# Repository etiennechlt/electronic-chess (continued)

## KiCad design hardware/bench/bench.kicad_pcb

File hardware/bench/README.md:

# Banc Nucleo : shield d'alimentation et de liaison du quadrant 2 x 2

Les deux faces tracées par KiCad, pours remplis (`tools/plot.py`) :
la face composants avec sa sérigraphie, puis la face masse vue
retournée, comme on regarde la carte réelle.

Carte générée par `tools/boardgen` (module `bench`) depuis la section
`bench` de `config/board.yaml`, pour le banc de la
[note 19](../../docs/notes/19-cerveau-et-banc-nucleo.md) : une
Nucleo-G474RE (le MCU du cerveau, sa sonde et son port série) qui
mesure le quadrant réduit 2 x 2 (`hardware/quadrant-2x2/`) avec le
firmware du cerveau compilé en `make NUCLEO=1`. Le shield apporte au
quadrant ce que le cerveau lui aurait donné, et rien d'autre.
80 x 56 mm, 2 couches : composants et signaux sur F.Cu, plan de masse
sur B.Cu. Elle s'emboîte sur les quatre embases Arduino de la Nucleo
par des barrettes mâles montées côté cuivre, corps sous la carte.

## Blocs

- **Embases Arduino** (J3 alimentation, J4 analogique, J5 numérique 0 à
  7, J6 numérique 8 à 15) : positions prises sur l'empreinte officielle
  `Arduino_UNO_R3`, contour Uno affleurant au bord ouest, bande de
  11,4 mm à l'est pour le jack et la nappe. Le bus du quadrant est sur
  les broches de `bench.signals` : AMP_OUT (après RC) sur A0, PULSE_EN
  sur A2, MUX_A0 à A2 sur D3, D4, D5, MUX_EN_L sur A5, MUX_EN_H sur A4,
  DAMP_EN_N sur D6, LED_DIN sur D13. Le shield prend le 3,3 V et la
  masse de la Nucleo ; son 5 V ne remonte jamais vers elle (la Nucleo
  reste sur l'USB de sa sonde), VIN, 5V, IOREF, NRST et AREF restent
  ouverts.
- **Entrée 12 V** (J1 jack 5,5 x 2,1 mm, prise vers l'est) : SS34 en
  série contre l'inversion, SMBJ15A vers la masse, fusible 1 A, puis
  100 µF, 10 µF et 100 nF : la réserve du rail d'impulsion, comme sur
  le cerveau, dans la colonne centrale entre le jack et le buck.
- **Buck 5 V** (TPS62130, 2,2 µH, DEF haut : PWM forcé) : le rail des
  LED à travers un second fusible 2 A et 100 µF, et l'alimentation du
  tampon LED. Colonne ouest, là où le motif Uno laisse le shield vide.
- **Îlot analogique 5VA** : LP2985-5.0 depuis le 12 V, perle de
  ferrite BLM21PG221, 10 µF et 100 nF, comme sur le cerveau. Le
  cavalier JP1 choisit la source de 5VA_RAW : broches 1 et 2, le LDO
  (défaut) ; 2 et 3, le buck. C'est la comparaison LDO contre buck de la
  mesure M8.
- **Liaison quadrant** : J2, FPC 16 broches Hirose FH12 au brochage du
  quadrant (`plateau.quadrant.link.pinout`), au coin sud-est, nappe
  vers le sud, pastilles vers le nord ; tampon 74AHCT1G125 (3,3 V vers
  5 V) et 470 ohms devant LED_DIN, LED_DOUT sur un point de test ;
  49,9 ohms et 1 nF devant A0, le filtre du cerveau.
- **Points de test** : TP1 LED_END (au coin sud-est, contre le
  connecteur FPC), TP2 5VA, TP3 5V, TP4 3V3, TP5 GND, TP6 VIN, TP7 ADC1
  (AMP_OUT filtré). Le bus de commande (PULSE_EN, DAMP_EN_N, adresses
  du mux) se sonde sur les broches Morpho de la Nucleo, qui doublent
  chaque broche Arduino.

## Ce qui se soude à la main

Le tampon LED, le buck, l'inductance, le LDO, la perle, les diodes,
le jack et le connecteur FPC reprennent les références du cerveau,
code LCSC compris. Les passifs, les quatre barrettes Arduino (côté
cuivre), JP1 et les points de test n'ont pas de code : `jlc-bom.csv`
ne liste que les lignes qui en ont un, le reste se soude à la main ou
attend la passe de sourcing des autres cartes.

## Régénérer

```bash
PYTHONPATH=tools .venv/bin/python -m boardgen build bench --render docs/images/bench.png
/usr/bin/python3 tools/plot.py hardware/bench/bench.kicad_pcb --out docs/images
```

La seconde commande, avec le Python de KiCad, remplit les pours et
trace les deux faces en SVG (`bench-top.svg`, `bench-bottom.svg`).

`tests/test_bench.py` vérifie que chaque signal du bus est sur la
broche du cerveau (sauf DAMP_EN_N, déplacé de PC2 à D6 parce que PC2
n'atteint qu'un connecteur Morpho), que chaque broche d'embase porte
le net que dit le yaml, que la nappe reprend le brochage du quadrant,
et que chaque broche de barrette tombe sur la pastille de l'empreinte
Uno qu'elle représente.

## Routes manuelles

Le routeur seul laissait six nets ouverts et, au DRC de KiCad, une
trentaine de connexions manquantes que son propre bilan ne voyait pas
(couloirs de sortie des vias d'éventail sans cuivre, pistes finissant
sur le coin arrondi d'une pastille, voir la
[note 04](../../docs/notes/04-routeur-et-garanties.md)). La carte se
finit donc comme dans pcbnew, mais dans le générateur, par des routes
manuelles (`hand_routes` de `tools/boardgen/bench.py`) que chaque
build redessine et vérifie :

- **Éventail du FPC** (J2, seize pastilles au pas de 0,5 mm) : pas de
  via d'éventail dans le plan de masse ; chaque broche quitte son
  moignon sur une colonne de 0,2 mm et tourne à sa hauteur dans une
  voie de 0,3 mm, vers l'ouest pour 5VA, AMP_OUT1, 3V3 et 5V_LED, vers
  l'est pour MUX_EN_L, MUX_EN_H, LED_END et PULSE_EN, la broche la
  plus extérieure d'abord, la suivante une voie plus haut, si bien
  qu'aucune voie ne croise une colonne ; les fins de voies sont
  décalées pour laisser un via au bout de chacune. MUX_A0, MUX_A1,
  MUX_A2 et DAMP_EN_N prennent un petit via aux rangées d'éventail et
  passent en face arrière sous le connecteur, puis sous l'embase J5
  jusqu'à leurs broches ; VIN et LED_DIN1 de même vers le nord. Les
  deux broches de masse tombent au plan par un via au bout de leur
  piste d'envol.
- **Bande est** : MUX_EN_L monte en face avant jusqu'à la rangée de J4
  et entre dans la dernière broche par le bout de la rangée, MUX_EN_H
  passe au-dessus de la rangée, PULSE_EN monte en face arrière le long
  du bord (les deux se croiseraient sinon), LED_END rejoint TP1.
- **Face nord** : 3V3 monte à l'ouest de C9, passe sous les embases
  jusqu'à J3, continue vers l'ouest et redescend entre C6 et R3 vers
  TP4 et C14 ; 5V_LED et AMP_OUT1 suivent, une voie plus bas chacune,
  jusqu'au fusible des LED et au filtre de l'ADC, 5V_LED sautant en
  face arrière sur deux millimètres pour franchir la montée de 3V3 ;
  VIN traverse la carte en face arrière à mi-hauteur jusqu'à TP6.
- **Buck** : une barrette de 0,2 mm sur les bouts de moignons relie
  les trois pastilles SW, une autre les trois VIN (le routeur posait
  une piste de puissance le long d'une piste d'envol, à 0,10 mm du
  moignon voisin) ; SW part en face arrière vers l'inductance, VIN vers
  un via à l'est de C4 puis le condensateur d'entrée, la pastille 5 V
  du côté nord suit son couloir de sortie ; les quatre pastilles de
  masse du QFN sont pontées à son pad thermique.
- **Masses murées** : la pastille de masse du LDO (entre ses deux
  VIN) et celle de R4 ont un moignon et un petit via vers le plan.

Chaque route manuelle est vérifiée au build par le contrôle
d'isolement exact contre le cuivre déjà posé ; le routeur part de ces
routes et termine chaque net. Un déplacement de composant qui les
rendrait fausses fait échouer le build.

## Résultat du build

Généré par `python -m boardgen build bench` :

| Composants | Segments | Vias | Nets fermés | Nets ouverts | Défauts d'isolement |
|---|---|---|---|---|---|
| 43 | 263 | 72 | 29 | 0 | 0 |

Tous les nets sont fermés : le contrôle de connexité partagé des
générateurs (`tools/quadgen/connect.py`, chaque net une seule pièce de
cuivre, plan de masse compris, [note 04](../../docs/notes/04-routeur-et-garanties.md))
ne signale rien, `tests/test_bench.py` le vérifie à chaque exécution.

DRC KiCad 7.0.11 (`/usr/bin/python3 tools/drc.py
hardware/bench/bench.kicad_pcb`, zones remplies) : zéro erreur, zéro
élément non connecté ; 83 avertissements, tous ignorables : 43
chemins de bibliothèque des empreintes (la configuration de KiCad ne
connaît pas les bibliothèques par leur nom), 35 de sérigraphie
(références sur une ligne ou une pastille), 5 vias d'éventail du QFN
raccordés d'un seul côté (la route est partie en face avant).

## Gerbers de fabrication

`bench-gerbers.zip` se dépose tel quel chez le fabricant : 2 couches
(F.Cu, B.Cu), la pâte de la face composants, les deux sérigraphies,
les deux masques, le contour et les perçages Excellon séparés (PTH et
NPTH), plus le fichier de tâche `.gbrjob`. 1,6 mm, finition HASL sans
plomb ou ENIG ; les options de commande et la nomenclature sont dans
la [note 20](../../docs/notes/20-tuto-banc.md), section 3.

À côté de l'archive, `<carte>-gerbers.sha256` porte l'empreinte de la
carte tracée et celle de l'archive. À vérifier avant toute commande :

```bash
cd hardware/bench && sha256sum -c bench-gerbers.sha256
```

Options écran par écran, quantités et décisions à trancher : la
[note 23](../../docs/notes/23-commande-jlcpcb.md).

```bash
/usr/bin/python3 tools/gerbers.py hardware/bench/bench.kicad_pcb
```

Avec le Python de KiCad : l'outil remplit les pours d'une copie de la
carte avant de tracer (sans ce remplissage le plan de masse de B.Cu
sort vide), lit le jeu de couches sur la carte, et refuse d'exporter
tant qu'une pastille reste non connectée. Le dossier `gerbers/` qu'il
écrit n'est pas versionné ; l'archive l'est.

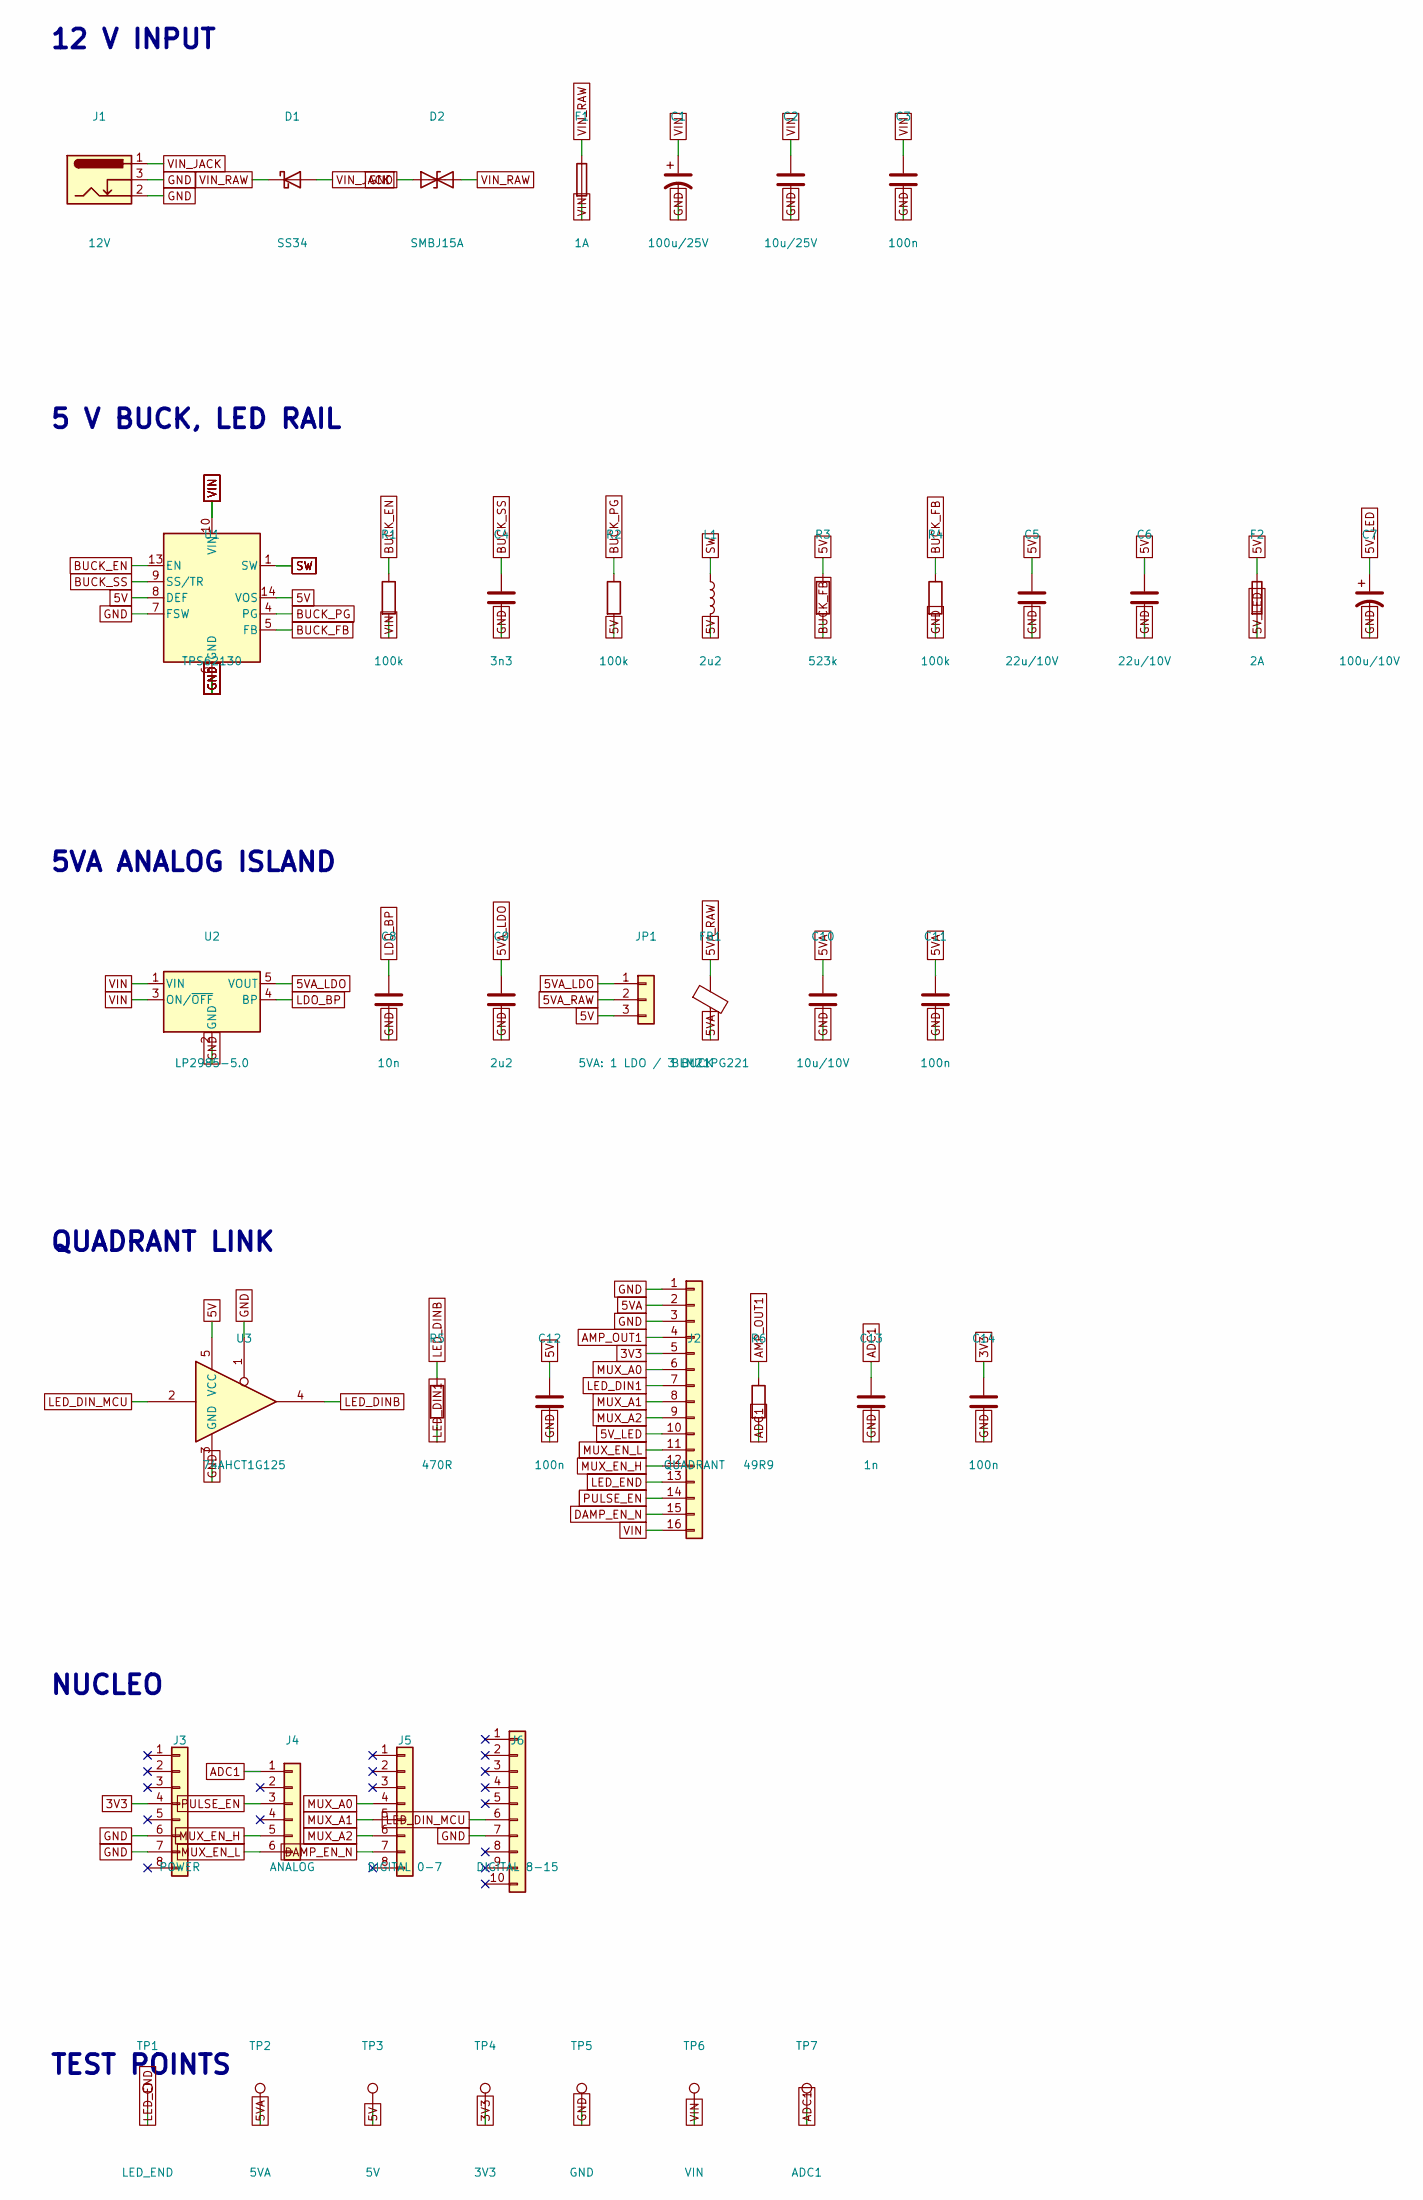
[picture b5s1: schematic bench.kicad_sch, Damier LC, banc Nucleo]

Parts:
C1: 100u/25V; CP_Elec_6.3x7.7
C2: 10u/25V; C_1206_3216Metric
C3, C11, C12, C14: 100n; C_0603_1608Metric
C4: 3n3; C_0603_1608Metric
C5, C6: 22u/10V; C_1206_3216Metric
C7: 100u/10V; CP_Elec_6.3x7.7
C8: 10n; C_0603_1608Metric
C9: 2u2; C_0603_1608Metric
C10: 10u/10V; C_1206_3216Metric
C13: 1n; C_0603_1608Metric
D1: SS34; D_SMA; MPN SS34; LCSC C8678
D2: SMBJ15A; D_SMB; MPN SMBJ15A; LCSC C113962
F1: 1A; Fuse_1206_3216Metric
F2: 2A; Fuse_1206_3216Metric
FB1: BLM21PG221; R_0805_2012Metric; MPN BLM21PG221SN1D; LCSC C18305
J1: 12V; BarrelJack_Horizontal; MPN DC-005-5.5x2.1; LCSC C381118
J2: QUADRANT; Hirose_FH12-16S-0.5SH_1x16-1MP_P0.50mm_Horizontal; MPN FH12-16S-0.5SH(55); LCSC C2837584
J3: POWER; PinHeader_1x08_P2.54mm_Vertical
J4: ANALOG; PinHeader_1x06_P2.54mm_Vertical
J5: DIGITAL 0-7; PinHeader_1x08_P2.54mm_Vertical
J6: DIGITAL 8-15; PinHeader_1x10_P2.54mm_Vertical
JP1: 5VA: 1 LDO / 3 BUCK; PinHeader_1x03_P2.54mm_Vertical
L1: 2u2; L_Bourns_SRN6045TA; MPN SRN6045TA-2R2M; LCSC C167219
R1, R2, R4: 100k; R_0603_1608Metric
R3: 523k; R_0603_1608Metric
R5: 470R; R_0603_1608Metric
R6: 49R9; R_0603_1608Metric
TP1: LED_END; TestPoint_Pad_1.5x1.5mm
TP2: 5VA; TestPoint_Pad_1.5x1.5mm
TP3: 5V; TestPoint_Pad_1.5x1.5mm
TP4: 3V3; TestPoint_Pad_1.5x1.5mm
TP5: GND; TestPoint_Pad_1.5x1.5mm
TP6: VIN; TestPoint_Pad_1.5x1.5mm
TP7: ADC1; TestPoint_Pad_1.5x1.5mm
U1: TPS62130; QFN-16-1EP_3x3mm_P0.5mm_EP1.75x1.75mm; MPN TPS62130RGTR; LCSC C74016
U2: LP2985-5.0; SOT-23-5; MPN LP2985AIM5-5.0; LCSC C129541
U3: 74AHCT1G125; SOT-23-5; MPN SN74AHCT1G125DBVR; LCSC C350557

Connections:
3V3: C14.1, J2.5, J3.4, TP4.1
5V: C5.1, C6.1, C12.1, F2.1, JP1.3, L1.2, R2.2, R3.1, TP3.1, U1.8 (DEF), U1.14 (VOS), U3.5 (VCC)
5VA: C10.1, C11.1, FB1.2, J2.2, TP2.1
5VA_LDO: C9.1, JP1.1, U2.5 (VOUT)
5VA_RAW: FB1.1, JP1.2
5V_LED: C7.1, F2.2, J2.10
ADC1: C13.1, J4.1, R6.2, TP7.1
AMP_OUT1: J2.4, R6.1
BUCK_EN: R1.1, U1.13 (EN)
BUCK_FB: R3.2, R4.1, U1.5 (FB)
BUCK_PG: R2.1, U1.4 (PG)
BUCK_SS: C4.1, U1.9 (SS/TR)
DAMP_EN_N: J2.15, J5.7
GND: C1.2, C2.2, C3.2, C4.2, C5.2, C6.2, C7.2, C8.2, C9.2, C10.2, C11.2, C12.2, C13.2, C14.2, D2.1 (A1), J1.2, J1.3, J2.1, J2.3, J3.6, J3.7, J6.7, R4.2, TP5.1, U1.6 (GND), U1.7 (FSW), U1.15 (GND), U1.16 (GND), U1.17 (GND), U2.2 (GND), U3.1, U3.3 (GND)
LDO_BP: C8.1, U2.4 (BP)
LED_DIN1: J2.7, R5.2
LED_DINB: R5.1, U3.4
LED_DIN_MCU: J6.6, U3.2
LED_END: J2.13, TP1.1
MUX_A0: J2.6, J5.4
MUX_A1: J2.8, J5.5
MUX_A2: J2.9, J5.6
MUX_EN_H: J2.12, J4.5
MUX_EN_L: J2.11, J4.6
PULSE_EN: J2.14, J4.3
SW: L1.1, U1.1 (SW), U1.2 (SW), U1.3 (SW)
VIN: C1.1, C2.1, C3.1, F1.2, J2.16, R1.2, TP6.1, U1.10 (VIN), U1.11 (VIN), U1.12 (VIN), U2.1 (VIN), U2.3 (ON/~OFF)
VIN_JACK: D1.2 (A), J1.1
VIN_RAW: D1.1 (K), D2.2 (A2), F1.1

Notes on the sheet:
12 V INPUT
5 V BUCK, LED RAIL
5VA ANALOG ISLAND
QUADRANT LINK
NUCLEO
TEST POINTS

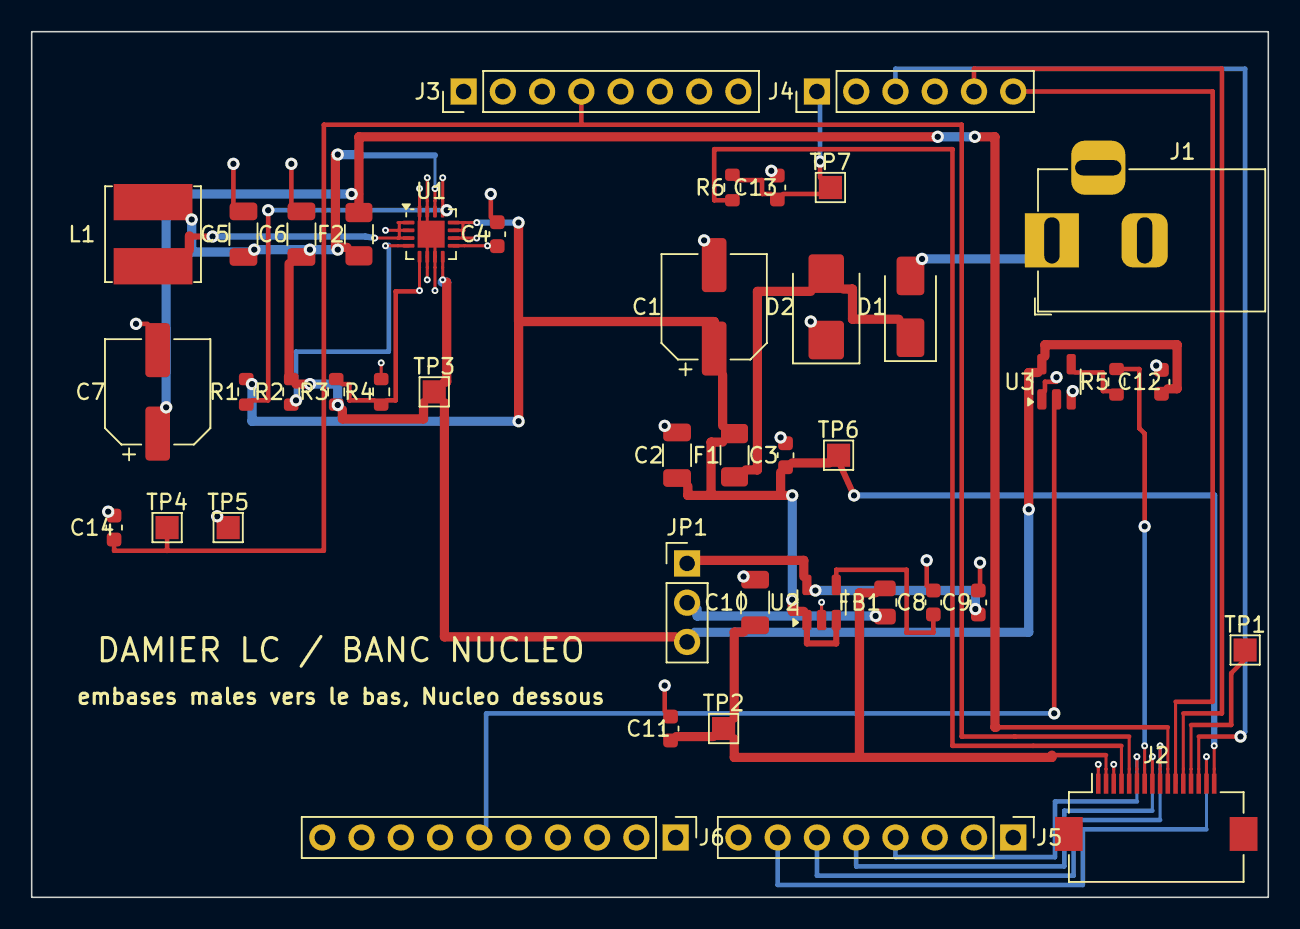
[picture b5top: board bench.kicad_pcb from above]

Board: 2 copper layers, 80.0 x 56.0 mm, 43 parts (0 on the bottom side), 29 nets.

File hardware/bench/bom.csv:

References,Qty,Value,Footprint,MPN,LCSC,DNP
C1,1,100u/25V,CP_Elec_6.3x7.7,,,
C10,1,10u/10V,C_1206_3216Metric,,,
C13,1,1n,C_0603_1608Metric,,,
C2,1,10u/25V,C_1206_3216Metric,,,
C11 C12 C14 C3,4,100n,C_0603_1608Metric,,,
C4,1,3n3,C_0603_1608Metric,,,
C5 C6,2,22u/10V,C_1206_3216Metric,,,
C7,1,100u/10V,CP_Elec_6.3x7.7,,,
C8,1,10n,C_0603_1608Metric,,,
C9,1,2u2,C_0603_1608Metric,,,
D1,1,SS34,D_SMA,SS34,C8678,
D2,1,SMBJ15A,D_SMB,SMBJ15A,C113962,
F1,1,1A,Fuse_1206_3216Metric,,,
F2,1,2A,Fuse_1206_3216Metric,,,
FB1,1,BLM21PG221,R_0805_2012Metric,BLM21PG221SN1D,C18305,
J1,1,12V,BarrelJack_Horizontal,DC-005-5.5x2.1,C381118,
J2,1,QUADRANT,Hirose_FH12-16S-0.5SH_1x16-1MP_P0.50mm_Horizontal,FH12-16S-0.5SH(55),C2837584,
J3,1,POWER,PinHeader_1x08_P2.54mm_Vertical,,,
J4,1,ANALOG,PinHeader_1x06_P2.54mm_Vertical,,,
J5,1,DIGITAL 0-7,PinHeader_1x08_P2.54mm_Vertical,,,
J6,1,DIGITAL 8-15,PinHeader_1x10_P2.54mm_Vertical,,,
JP1,1,5VA: 1 LDO / 3 BUCK,PinHeader_1x03_P2.54mm_Vertical,,,
L1,1,2u2,L_Bourns_SRN6045TA,SRN6045TA-2R2M,C167219,
R1 R2 R4,3,100k,R_0603_1608Metric,,,
R3,1,523k,R_0603_1608Metric,,,
R5,1,470R,R_0603_1608Metric,,,
R6,1,49R9,R_0603_1608Metric,,,
TP1,1,LED_END,TestPoint_Pad_1.5x1.5mm,,,
TP2,1,5VA,TestPoint_Pad_1.5x1.5mm,,,
TP3,1,5V,TestPoint_Pad_1.5x1.5mm,,,
TP4,1,3V3,TestPoint_Pad_1.5x1.5mm,,,
TP5,1,GND,TestPoint_Pad_1.5x1.5mm,,,
TP6,1,VIN,TestPoint_Pad_1.5x1.5mm,,,
TP7,1,ADC1,TestPoint_Pad_1.5x1.5mm,,,
U1,1,TPS62130,QFN-16-1EP_3x3mm_P0.5mm_EP1.75x1.75mm,TPS62130RGTR,C74016,
U2,1,LP2985-5.0,SOT-23-5,LP2985AIM5-5.0,C129541,
U3,1,74AHCT1G125,SOT-23-5,SN74AHCT1G125DBVR,C350557,

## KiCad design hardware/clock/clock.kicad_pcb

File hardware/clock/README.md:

# Horloge à bascule : carte

Générée par `tools/boardgen` (module `clock`). 110 x 60 mm, 2 couches,
dans le boîtier de `mechanical/clock.py`.

- **Radio et calcul** : module ESP32-S3-WROOM-1 (le même que sur le
  cerveau, BLE vers le plateau), antenne hors du bord est, cour réduite
  à la largeur du module (l'encodeur et un microrupteur sont de part et
  d'autre, choix assumé pour du BLE à courte portée), boutons BOOT et
  EN, embase de programmation 1 x 6, diviseur de tension batterie sur
  IO1, état du chargeur sur IO2 par un diviseur 56 k / 100 k (STAT monte
  à 5 V).
- **Énergie** : USB-C en alimentation seule (5,1 k sur CC, D+, D- et SBU
  non connectés), chargeur 1S MCP73831 à 500 mA avec LED d'état,
  support 18650 Keystone 1042, embase pour l'interrupteur, AP2112K 3,3 V.
- **Interface** : embase 1 x 14 pour un écran 2,4 pouces ILI9341 SPI
  avec tactile, rétroéclairage commuté par un P-FET AO3401A sur 3V3
  (IO7 actif bas, éteint au démarrage), deux microrupteurs 6 x 6 sous
  les extrémités de la
  barre à bascule (positions dérivées de `clock.rocker` du yaml, la
  carte étant à 5 mm des parois du boîtier), encodeur EC11 à poussoir
  à l'avant droit sous son trou de la face inclinée, buzzer 12 mm sur
  transistor, USB-C dans la fente arrière.

```bash
PYTHONPATH=tools .venv/bin/python -m boardgen build clock --render docs/images/clock.png
```

## Résultat du build

Généré par `python -m boardgen build clock` :

| Composants | Segments | Vias | Nets fermés | Nets ouverts | Défauts d'isolement |
|---|---|---|---|---|---|
| 50 | 307 | 149 | 31 | 6 | 0 |

Nets à finir dans pcbnew (le routeur les a laissés ouverts) :
- CHG_SENSE: 1 pad(s) left open (usable start cells 77, goal cells 85)
- CC2: 2 pad(s) left open (usable start cells 8, goal cells 50)
- GND: pad at cell (131, 39) has no drop to the pour
- GND: pad at cell (149, 30) has no drop to the pour
- GND: pad at cell (464, 98) has no drop to the pour
- GND: pad at cell (542, 102) has no drop to the pour

DRC KiCad 7 (`tools/drc.py`, zones remplies) : 178 signalements, 51 éléments non connectés (les nets ouverts ci-dessus), erreurs restantes : aucune ; avertissements sans effet sur la fabrication : via_dangling 53, lib_footprint_issues 50, silk_overlap 38, track_dangling 28, silk_over_copper 8, silk_edge_clearance 1. Le contrôle d'isolement exact du générateur ne signale aucun défaut. Les vias d'éventail des boîtiers fins font 0,45 mm (perçage 0,2 mm), dans les capacités standard de JLCPCB, à confirmer sur le devis.

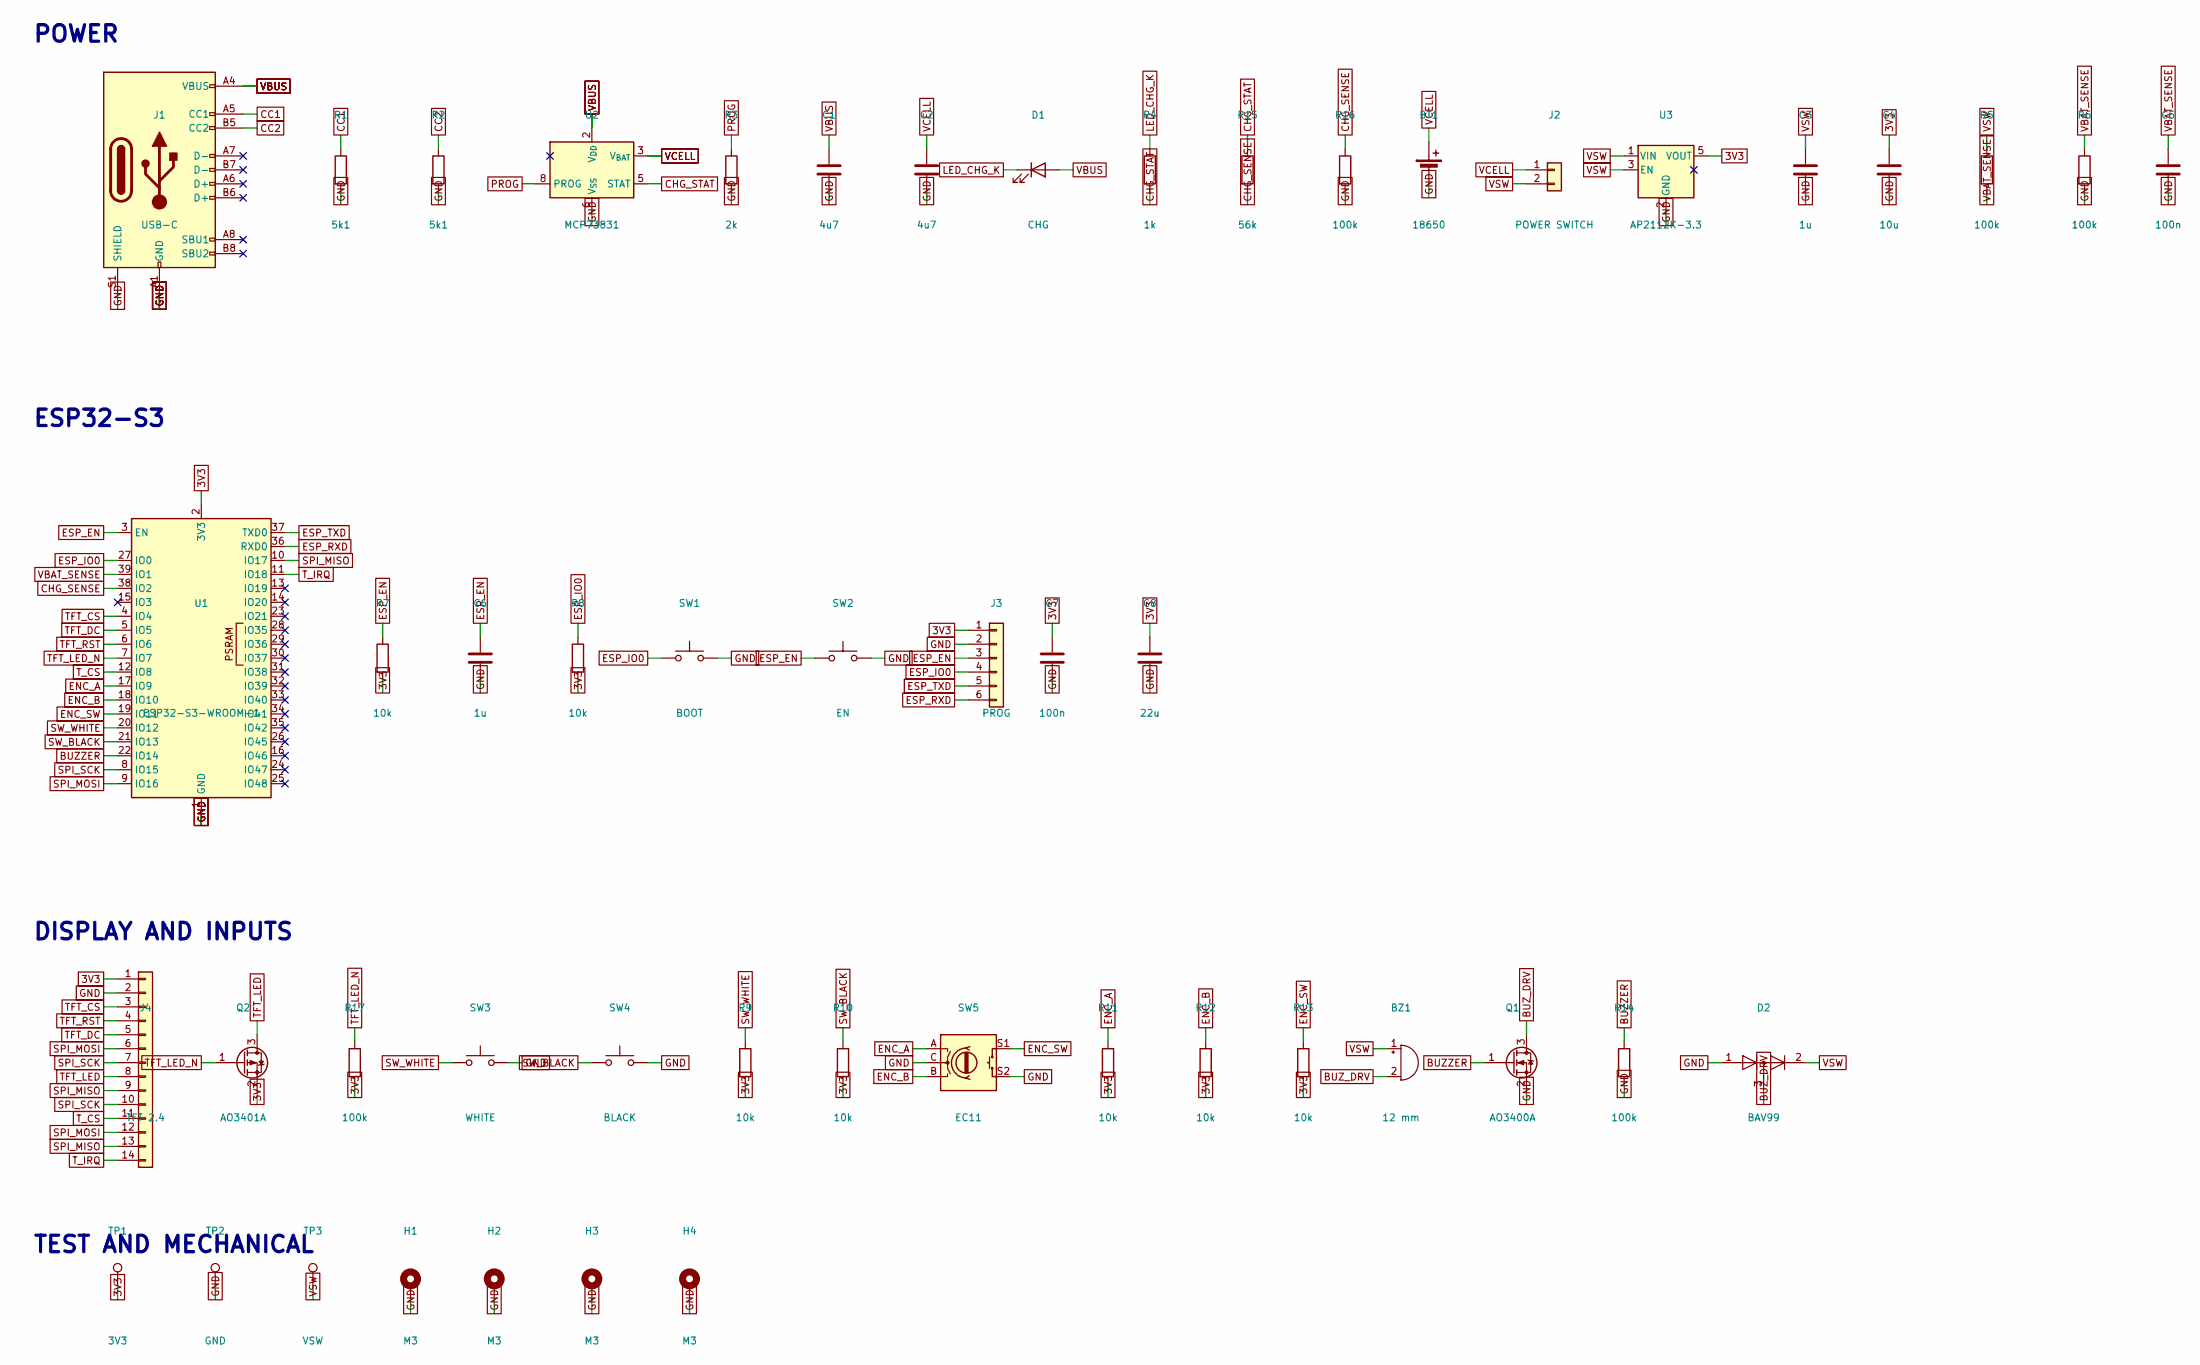
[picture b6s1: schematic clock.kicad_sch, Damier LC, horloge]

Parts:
BT1: 18650; BatteryHolder_Keystone_1042_1x18650
BZ1: 12 mm; Buzzer_12x9.5RM7.6
C1, C2: 4u7; C_0603_1608Metric
C3, C6: 1u; C_0603_1608Metric
C4: 10u; C_0603_1608Metric
C5, C7: 100n; C_0603_1608Metric
C8: 22u; C_0603_1608Metric
D1: CHG; LED_0603_1608Metric
D2: BAV99; SOT-23; MPN BAV99; LCSC C2500
H1, H2, H3, H4: M3; MountingHole_3.2mm_M3_Pad
J1: USB-C; USB_C_Receptacle_GCT_USB4085; MPN USB4085-GF-A; LCSC C2988369
J2: POWER SWITCH; PinHeader_1x02_P2.54mm_Vertical
J3: PROG; PinHeader_1x06_P2.54mm_Vertical
J4: TFT 2.4; PinHeader_1x14_P2.54mm_Vertical
Q1: AO3400A; SOT-23; MPN AO3400A; LCSC C20917
Q2: AO3401A; SOT-23; MPN AO3401A; LCSC C15127
R1, R2: 5k1; R_0603_1608Metric
R3: 2k; R_0603_1608Metric
R4: 1k; R_0603_1608Metric
R5, R6, R14, R16, R17: 100k; R_0603_1608Metric
R7, R8, R9, R10, R11, R12, R13: 10k; R_0603_1608Metric
R15: 56k; R_0603_1608Metric
SW1: BOOT; SW_SPST_PTS645; MPN PTS645SM43SMTR92; LCSC C221929
SW2: EN; SW_SPST_PTS645; MPN PTS645SM43SMTR92; LCSC C221929
SW3: WHITE; SW_PUSH_6mm_H4.3mm; MPN TS-1187A
SW4: BLACK; SW_PUSH_6mm_H4.3mm; MPN TS-1187A
SW5: EC11; RotaryEncoder_Alps_EC11E-Switch_Vertical_H20mm; MPN EC11E15244B2
TP1: 3V3; TestPoint_Pad_1.5x1.5mm
TP2: GND; TestPoint_Pad_1.5x1.5mm
TP3: VSW; TestPoint_Pad_1.5x1.5mm
U1: ESP32-S3-WROOM-1; MPN ESP32-S3-WROOM-1-N8; LCSC C2913204
U2: MCP73831; DFN-8-1EP_2x3mm_P0.5mm_EP0.61x2.2mm; MPN MCP73831T-2ACI/MC; LCSC C424093
U3: AP2112K-3.3; SOT-23-5; MPN AP2112K-3.3TRG1; LCSC C51118

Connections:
3V3: C4.1, C7.1, C8.1, J3.1, J4.1, Q2.2 (S), R7.2, R8.2, R9.2, R10.2, R11.2, R12.2, R13.2, R17.2, TP1.1, U1.2 (3V3), U3.5 (VOUT)
BUZZER: Q1.1 (G), R14.1, U1.22 (IO14)
BUZ_DRV: BZ1.2 (-), D2.3 (K), Q1.3 (D)
CC1: J1.A5 (CC1), R1.1
CC2: J1.B5 (CC2), R2.1
CHG_SENSE: R15.2, R16.1, U1.38 (IO2)
CHG_STAT: R4.2, R15.1, U2.5 (STAT)
ENC_A: R11.1, SW5.A, U1.17 (IO9)
ENC_B: R12.1, SW5.B, U1.18 (IO10)
ENC_SW: R13.1, SW5.S1, U1.19 (IO11)
ESP_EN: C6.1, J3.3, R7.1, SW2.1, U1.3 (EN)
ESP_IO0: J3.4, R8.1, SW1.1, U1.27 (IO0)
ESP_RXD: J3.6, U1.36 (RXD0)
ESP_TXD: J3.5, U1.37 (TXD0)
GND: BT1.2 (-), C1.2, C2.2, C3.2, C4.2, C5.2, C6.2, C7.2, C8.2, D2.1 (K), H1.1, H2.1, H3.1, H4.1, J1.A1 (GND), J1.A12 (GND), J1.B1 (GND), J1.B12 (GND), J1.S1 (SHIELD), J3.2, J4.2, Q1.2 (S), R1.2, R2.2, R3.2, R6.2, R14.2, R16.2, SW1.2, SW2.2, SW3.2, SW4.2, SW5.C, SW5.S2, TP2.1, U1.1 (GND), U1.40 (GND), U1.41 (GND), U2.6 (V_{SS}), U3.2 (GND)
LED_CHG_K: D1.1 (K), R4.1
PROG: R3.1, U2.8 (PROG)
SPI_MISO: J4.9, J4.13, U1.10 (IO17)
SPI_MOSI: J4.6, J4.12, U1.9 (IO16)
SPI_SCK: J4.7, J4.10, U1.8 (IO15)
SW_BLACK: R10.1, SW4.1, U1.21 (IO13)
SW_WHITE: R9.1, SW3.1, U1.20 (IO12)
TFT_CS: J4.3, U1.4 (IO4)
TFT_DC: J4.5, U1.5 (IO5)
TFT_LED: J4.8, Q2.3 (D)
TFT_LED_N: Q2.1 (G), R17.1, U1.7 (IO7)
TFT_RST: J4.4, U1.6 (IO6)
T_CS: J4.11, U1.12 (IO8)
T_IRQ: J4.14, U1.11 (IO18)
VBAT_SENSE: C5.1, R5.2, R6.1, U1.39 (IO1)
VBUS: C1.1, D1.2 (A), J1.A4 (VBUS), J1.A9 (VBUS), J1.B4 (VBUS), J1.B9 (VBUS), U2.1 (V_{DD}), U2.2 (V_{DD})
VCELL: BT1.1 (+), C2.1, J2.1, U2.3 (V_{BAT}), U2.4 (V_{BAT})
VSW: BZ1.1 (+), C3.1, D2.2 (A), J2.2, R5.1, TP3.1, U3.1 (VIN), U3.3 (EN)

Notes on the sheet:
POWER
ESP32-S3
DISPLAY AND INPUTS
TEST AND MECHANICAL

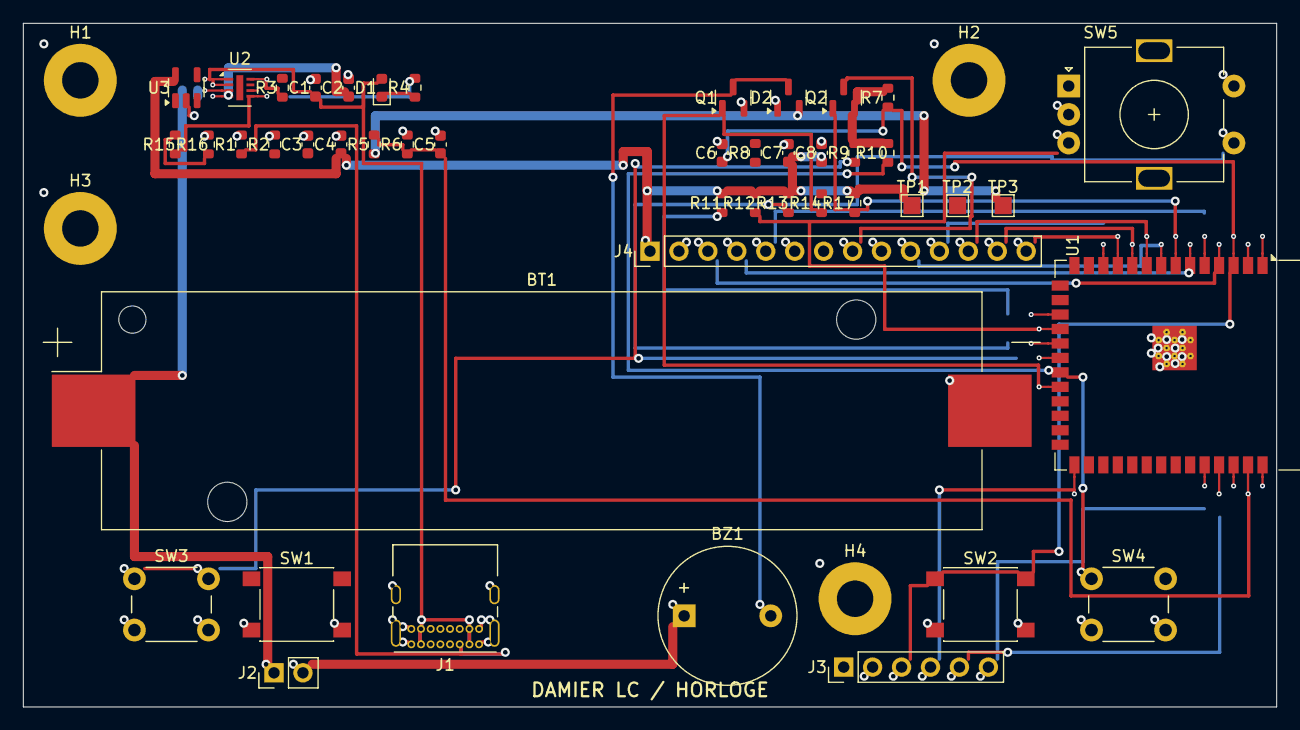
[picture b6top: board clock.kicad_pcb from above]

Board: 2 copper layers, 110.0 x 60.0 mm, 50 parts (0 on the bottom side), 33 nets.

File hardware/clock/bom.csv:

References,Qty,Value,Footprint,MPN,LCSC,DNP
BT1,1,18650,BatteryHolder_Keystone_1042_1x18650,,,
BZ1,1,12 mm,Buzzer_12x9.5RM7.6,,,
C1 C2,2,4u7,C_0603_1608Metric,,,
C3 C6,2,1u,C_0603_1608Metric,,,
C4,1,10u,C_0603_1608Metric,,,
C5 C7,2,100n,C_0603_1608Metric,,,
C8,1,22u,C_0603_1608Metric,,,
D1,1,CHG,LED_0603_1608Metric,,,
D2,1,BAV99,SOT-23,BAV99,C2500,
H1 H2 H3 H4,4,M3,MountingHole_3.2mm_M3_Pad,,,
J1,1,USB-C,USB_C_Receptacle_GCT_USB4085,USB4085-GF-A,C2988369,
J2,1,POWER SWITCH,PinHeader_1x02_P2.54mm_Vertical,,,
J3,1,PROG,PinHeader_1x06_P2.54mm_Vertical,,,
J4,1,TFT 2.4,PinHeader_1x14_P2.54mm_Vertical,,,
Q1,1,AO3400A,SOT-23,AO3400A,C20917,
Q2,1,AO3401A,SOT-23,AO3401A,C15127,
R1 R2,2,5k1,R_0603_1608Metric,,,
R15,1,56k,R_0603_1608Metric,,,
R14 R16 R17 R5 R6,5,100k,R_0603_1608Metric,,,
R3,1,2k,R_0603_1608Metric,,,
R4,1,1k,R_0603_1608Metric,,,
R10 R11 R12 R13 R7 R8 R9,7,10k,R_0603_1608Metric,,,
SW1,1,BOOT,SW_SPST_PTS645,PTS645SM43SMTR92,C221929,
SW2,1,EN,SW_SPST_PTS645,PTS645SM43SMTR92,C221929,
SW3,1,WHITE,SW_PUSH_6mm_H4.3mm,TS-1187A,,
SW4,1,BLACK,SW_PUSH_6mm_H4.3mm,TS-1187A,,
SW5,1,EC11,RotaryEncoder_Alps_EC11E-Switch_Vertical_H20mm,EC11E15244B2,,
TP1,1,3V3,TestPoint_Pad_1.5x1.5mm,,,
TP2,1,GND,TestPoint_Pad_1.5x1.5mm,,,
TP3,1,VSW,TestPoint_Pad_1.5x1.5mm,,,
U1,1,ESP32-S3-WROOM-1,ESP32-S3-WROOM-1,ESP32-S3-WROOM-1-N8,C2913204,
U2,1,MCP73831,DFN-8-1EP_2x3mm_P0.5mm_EP0.61x2.2mm,MCP73831T-2ACI/MC,C424093,
U3,1,AP2112K-3.3,SOT-23-5,AP2112K-3.3TRG1,C51118,
